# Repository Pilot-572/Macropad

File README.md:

# Macropad; 9 keys, 1 encoder and an OLED
(first time making a readme for a macropad so bear with me <3)

### Hello yall! So this is the forth project which I posted on Stardance! (let's just ignore the other 3)
The first 3 were software projects, but this one (as you may or may not saw) its a hardware project! **Hardware > Software**
A macropad, who wouldn't want that? Plus you make it yourself AND get funded from our dear friends from Stardance! Now, who wouldn't what **THAT**.

As you saw (actually you didnt but let's ignore that), the Hackpad consists of 2 parts, the bottom part, the case itself and the top panel which makes it look prettier.

It has 9 switches, 1 encoder and an OLED, the case is very lovely in my opinion can't wait to 3D print it and the firmware is as basic as it gets basically, I will make it better as I finish the hardware and start using it.

Right now only 3 keys and the encoder are in use, the encoder for the volume and the 3 keys for media, the only things I NEED to have to be able to LIVE.

## Here's the PCB

## And the Schematic

##

What else can I say, it has a 3x3 matrix with diodes, uses almost all the parts from the Hackpad kit (doesn't use the LEDs, screws, heat inserts and the extra switches and keycaps) and I have the XIAO on the BACK of the board to minimise the area of the board, to make it as compact as I can.
The top panel uses M2 screws with I will supply them myself and the case uses M2 heat inserts, same idea.

## BOM

|          Part          | Qty |Price|Link|
|------------------------|-----|----|-----|
| Seeed XIAO RP2040      |  1  |$3.90/18.53 RON|https://www.seeedstudio.com/XIAO-RP2040-v1-0-p-5026.html
| MX-Style Switches      |  9  |~$2.70/~12.82 RON|https://www.divinikey.com/products gateron-ks-3-milky-yellow-pro-linear-switches
| White DSA Keycaps      |  9  |  White DSA Keycaps,9,~$5.35/~25.44 RON|https://www.adafruit.com/product/4998
| EC11E Encoder          |  1  |EC11E Encoder,1,$5.74/27.26 RON|https://www.digikey.com/en/products/detail/alps-alpine/EC11E1820402/21721574
| 0.91 inch OLED Display |  1  |0.91 inch OLED Display,1,$3.90/18.52 RON|https://www.displaymodule.com/products/0-91-inch-oled-graphic-display-128x32-with-i2c
| 1N4148 Diodes          |  9  |1N4148 Diodes,9,$0.90/ 4.27 RON|https://www.digikey.com/en/products/detail/onsemi/1N4148/458603
| M2 Screws              |  4  |
| M2 Heat Inserts        |  4  |
| 3D Printed Case        |  1  |
| 3D Printed Panel       |  1  |

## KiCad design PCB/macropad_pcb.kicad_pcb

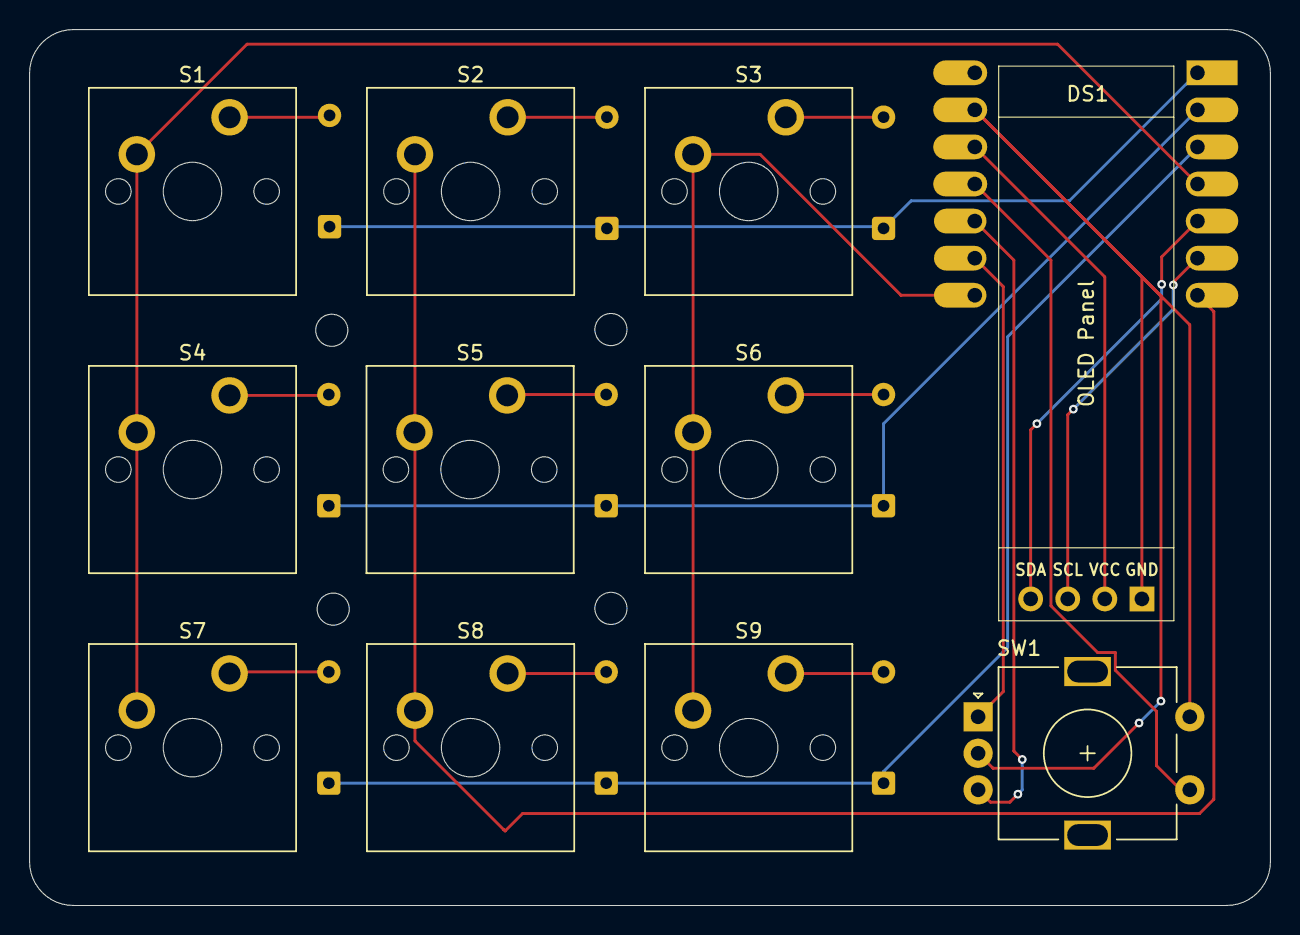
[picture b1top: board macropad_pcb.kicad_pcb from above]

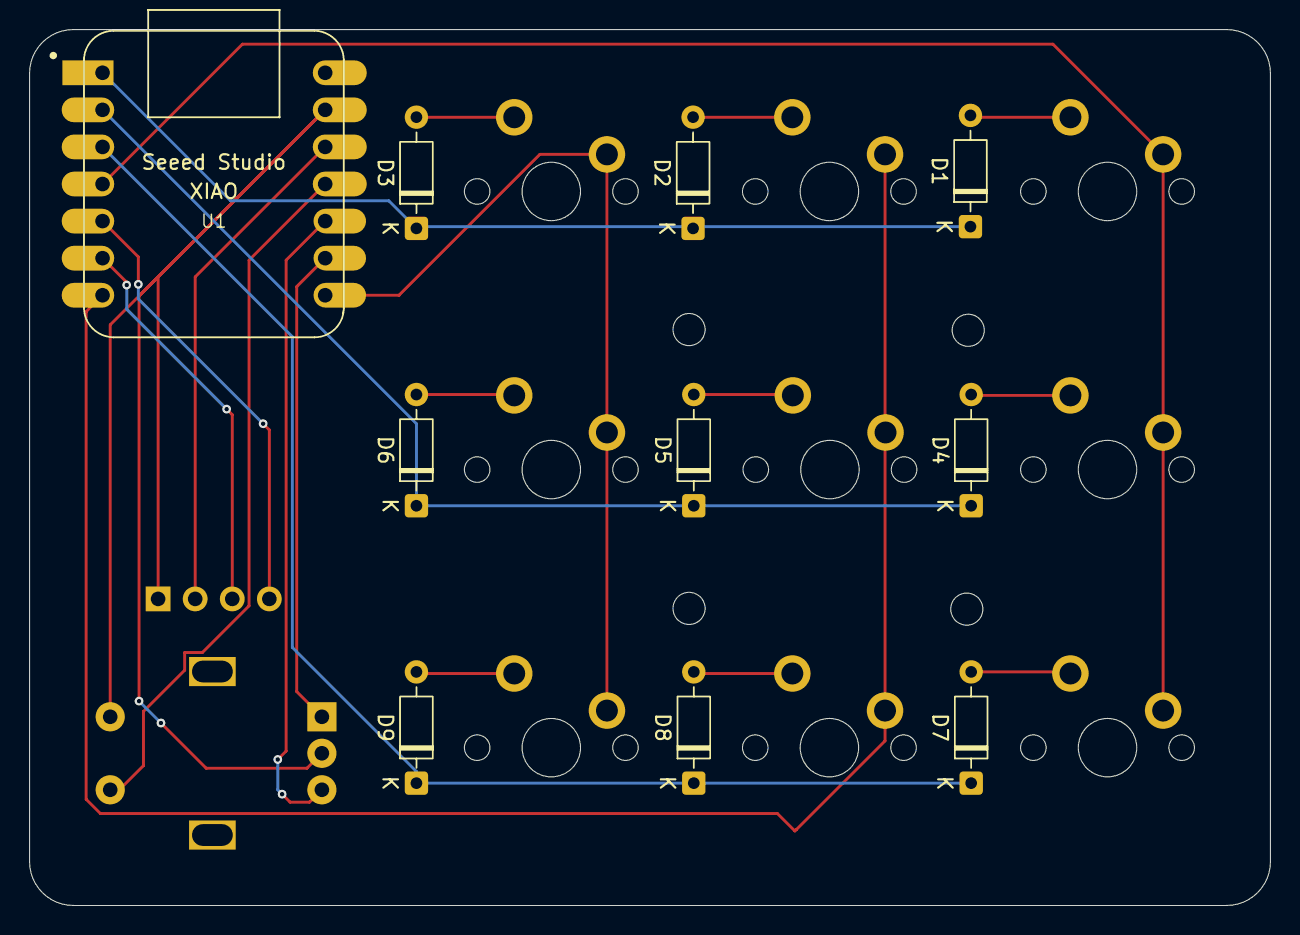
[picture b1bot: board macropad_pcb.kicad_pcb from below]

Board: 2 copper layers, 85.0 x 60.0 mm, 21 parts (10 on the bottom side), 22 nets.

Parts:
D1, D2, D3, D4, D5, D6, D7, D8, D9: 1N4148; D_DO-35_SOD27_P7.62mm_Horizontal
DS1: OLED_0.91_128x32_I2C; SSD1306-0.91-OLED-4pin-128x32
S1, S2, S3, S4, S5, S6, S7, S8, S9: MX_PCB_1.00u
SW1: RotaryEncoder_Switch; RotaryEncoder_Alps_EC11E-Switch_Vertical_H20mm
U1: MOUDLE-SEEEDUINO-XIAO; XIAO-Generic-Hybrid-14P-2.54-21X17.8MM

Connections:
+3.3V: DS1.2 (VCC), U1.12 (3V3)
Column 0: S1.1, S4.1, S7.1, U1.4 (PA11_A3_D3)
Column 1: S2.1, S5.1, S8.1, U1.7 (PB08_A6_D6_TX)
Column 2: S3.1, S6.1, S9.1, U1.8 (PB09_A7_D7_RX)
ENC_A: SW1.A, U1.9 (PA7_A8_D8_SCK)
ENC_B: SW1.B, U1.10 (PA5_A9_D9_MISO)
ENC_SW: SW1.S1, U1.11 (PA6_A10_D10_MOSI)
GND: DS1.1 (GND), SW1.C, SW1.S2, U1.13 (GND)
unnamed: D1.2 (A), S1.2
unnamed: D2.2 (A), S2.2
unnamed: D3.2 (A), S3.2
unnamed: D4.2 (A), S4.2
unnamed: D5.2 (A), S5.2
unnamed: D6.2 (A), S6.2
unnamed: D7.2 (A), S7.2
unnamed: D8.2 (A), S8.2
unnamed: D9.2 (A), S9.2
Row 0: D1.1 (K), D2.1 (K), D3.1 (K), U1.1 (PA02_A0_D0)
Row 1: D4.1 (K), D5.1 (K), D6.1 (K), U1.2 (PA4_A1_D1)
Row 2: D7.1 (K), D8.1 (K), D9.1 (K), U1.3 (PA10_A2_D2)
SCL: DS1.3 (SCL), U1.6 (PA9_A5_D5_SCL)
SDA: DS1.4 (SDA), U1.5 (PA8_A4_D4_SDA)
